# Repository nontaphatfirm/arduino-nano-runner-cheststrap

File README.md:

# Arduino Nano Runner Cheststrap

A wearable sensor system for runner form analysis built on the **Arduino Nano 33 BLE Sense Rev1**.  
Mounts on the chest or torso and streams 9-axis IMU data at 20 Hz to a Web Serial dashboard for real-time feedback.

---

## What It Measures

| Signal | Sensor | Insight |
|---|---|---|
| Acceleration (XYZ) | LSM9DS1 accelerometer (built-in) | Impact force, vertical oscillation, lean |
| Rotation rate (XYZ) | LSM9DS1 gyroscope (built-in) | Trunk lean, roll, yaw drift |
| Magnetic heading | LSM9DS1 magnetometer (built-in) | Absolute orientation reference |
| Ambient sound | OJFF14 analog sound sensor | Sound level / step rhythm |
| Visual capture | OV7675 camera | Keyframe image on demand |

---

## Hardware

### Main Board
**Arduino Nano 33 BLE Sense Rev1** (ABX00031) — Nordic nRF52480, ARM Cortex-M4F @ 64 MHz, 1 MB Flash / 256 KB RAM

Built-in sensors used:

| Chip | Function | I²C Address |
|---|---|---|
| LSM9DS1 | 9-axis IMU (accel + gyro + mag) | — (via library) |
| MP34DT05 | MEMS microphone | — (PDM) |
| APDS-9960 | Gesture / ambient light | 0x39 |
| ATECC608A | Crypto co-processor | — |

### External Sensors

| Component | Connection | Notes |
|---|---|---|
| OJFF14 Sound Sensor | S → A7, + → 3V3, − → GND | 3.3V supply; Nano analog pins are NOT 5V tolerant |
| OV7675 Camera | Arduino Tiny Machine Learning Shield | 8-bit DVP, SCCB config |

### Available Modulino Modules (Arduino Plug and Make Kit)
Connects to **Arduino UNO Q** via Qwiic chain (`Wire1`). Use Modulino library address in code — not the hardware scan address.

| Module | Chip | I²C Address | Specs |
|---|---|---|---|
| DISTANCE | VL53L4CDV0DH/1 (ToF laser) | 0x29 | 0–1200 mm, ±7 mm accuracy |
| THERMO | HS3003 | 0x44 | −40–125°C ±0.25°C / 0–100% RH ±2.8% |
| MOVEMENT | LSM6DSOXTR (6-axis IMU) | 0x6A | ±2–16 g / ±125–2000 dps |
| PIXELS | 8× LC8822-2020 RGB LEDs | 0x6C | 8-bit per channel, individually addressable |
| BUZZER | PKLCS1212E4001 passive buzzer | 0x3C | 31 Hz – 4186 Hz |
| KNOB | Quadrature rotary encoder | 0x76 | Rotary + press |
| BUTTONS | 3× SPST + LEDs | 0x7C | Tactile navigation |

---

## sensors-test — Main Sketch

> **This is the primary code for the project.**

```
sensors-test/
├── sensors_test/
│   └── sensors_test.ino   ← Arduino sketch (IMU + sound, 20 Hz JSON over Serial)
└── dashboard.html          ← Web Serial dashboard (Chrome / Edge)
```

### Serial Output

Streams newline-delimited JSON at 115200 baud, 20 Hz:

```json
{"type":"data","t":12345,"ax":0.12,"ay":0.03,"az":9.81,"gx":0.01,"gy":0.02,"gz":0.00,"mx":12.0,"my":4.0,"mz":39.0,"magReady":true,"soundRaw":2048,"soundPeak":120,"soundVolts":1.65,"soundLevel":0.13}
```

| Field | Unit | Description |
|---|---|---|
| ax, ay, az | m/s² | Acceleration |
| gx, gy, gz | rad/s | Angular velocity |
| mx, my, mz | µT | Magnetic field |
| soundRaw | 12-bit ADC avg | Mean ADC reading across 32 samples |
| soundPeak | 12-bit ADC pp | Peak-to-peak amplitude |
| soundVolts | V | Average voltage at A7 |
| soundLevel | 0–1 | Normalized sound activity |

### Dashboard Features
- Live XYZ acceleration charts
- Orientation: lean, roll, yaw
- Dead-reckoned 3D position estimate (integrate accel → velocity → displacement)
- Step cadence estimate from acceleration magnitude peaks
- Sound level visualization with sensitivity slider

### Required Libraries

Install via Arduino Library Manager:

| Board | Library |
|---|---|
| Nano 33 BLE Sense **Rev1** (default) | `Arduino_LSM9DS1` |
| Rev2 | `Arduino_BMI270_BMM150` — set `SENSOR_BOARD_REV 2` in sketch |

### Quick Start

1. Install `Arduino_LSM9DS1` from Arduino Library Manager.
2. Open `sensors-test/sensors_test/sensors_test.ino`.
3. Select board: **Arduino Nano 33 BLE**.
4. Upload.
5. Open `sensors-test/dashboard.html` in **Chrome** or **Edge**.
6. Click **Connect Serial** → select the Arduino port.
7. Hold the board still → click **Reset Tracking**.
8. Move like a runner torso: lean, bounce, side sway.

### OJFF14 Wiring

| OJFF14 pin | Nano 33 BLE Sense |
|---|---|
| S | A7 |
| + | 3V3 |
| − | GND |

> If powering OJFF14 from 5V, use a voltage divider or level shifter on the signal line — Nano 33 BLE analog inputs are not 5V tolerant.

---

## Repository Layout

| Path | Description |
|---|---|
| `sensors-test/` | **Main sketch + Web Serial dashboard** |
| `hardware/` | Datasheets (UNO Q, Modulino kit, Nano 33 BLE, OV7675, OJFF14) |
| `HARDWARE.md` | Full sensor specs, wiring, I²C addresses |
| `hardware-specs.md` | Concise hardware specification tables |
| `hardware-guide.md` | Beginner-friendly hardware walkthrough |
| `CLAUDE.md` | Project context |

---

## Board Identification

This project targets **Rev1** specifically (original Nano 33 BLE Sense).

USB descriptor confirms Rev1:
```
idVendor  : 0x2341  (Arduino)
idProduct : 0x805A
bcdDevice : 0x0101  (v1.01)
```

Rev2 uses different IMU chips (BMI270 + BMM150) — set `SENSOR_BOARD_REV 2` in the sketch if using Rev2.

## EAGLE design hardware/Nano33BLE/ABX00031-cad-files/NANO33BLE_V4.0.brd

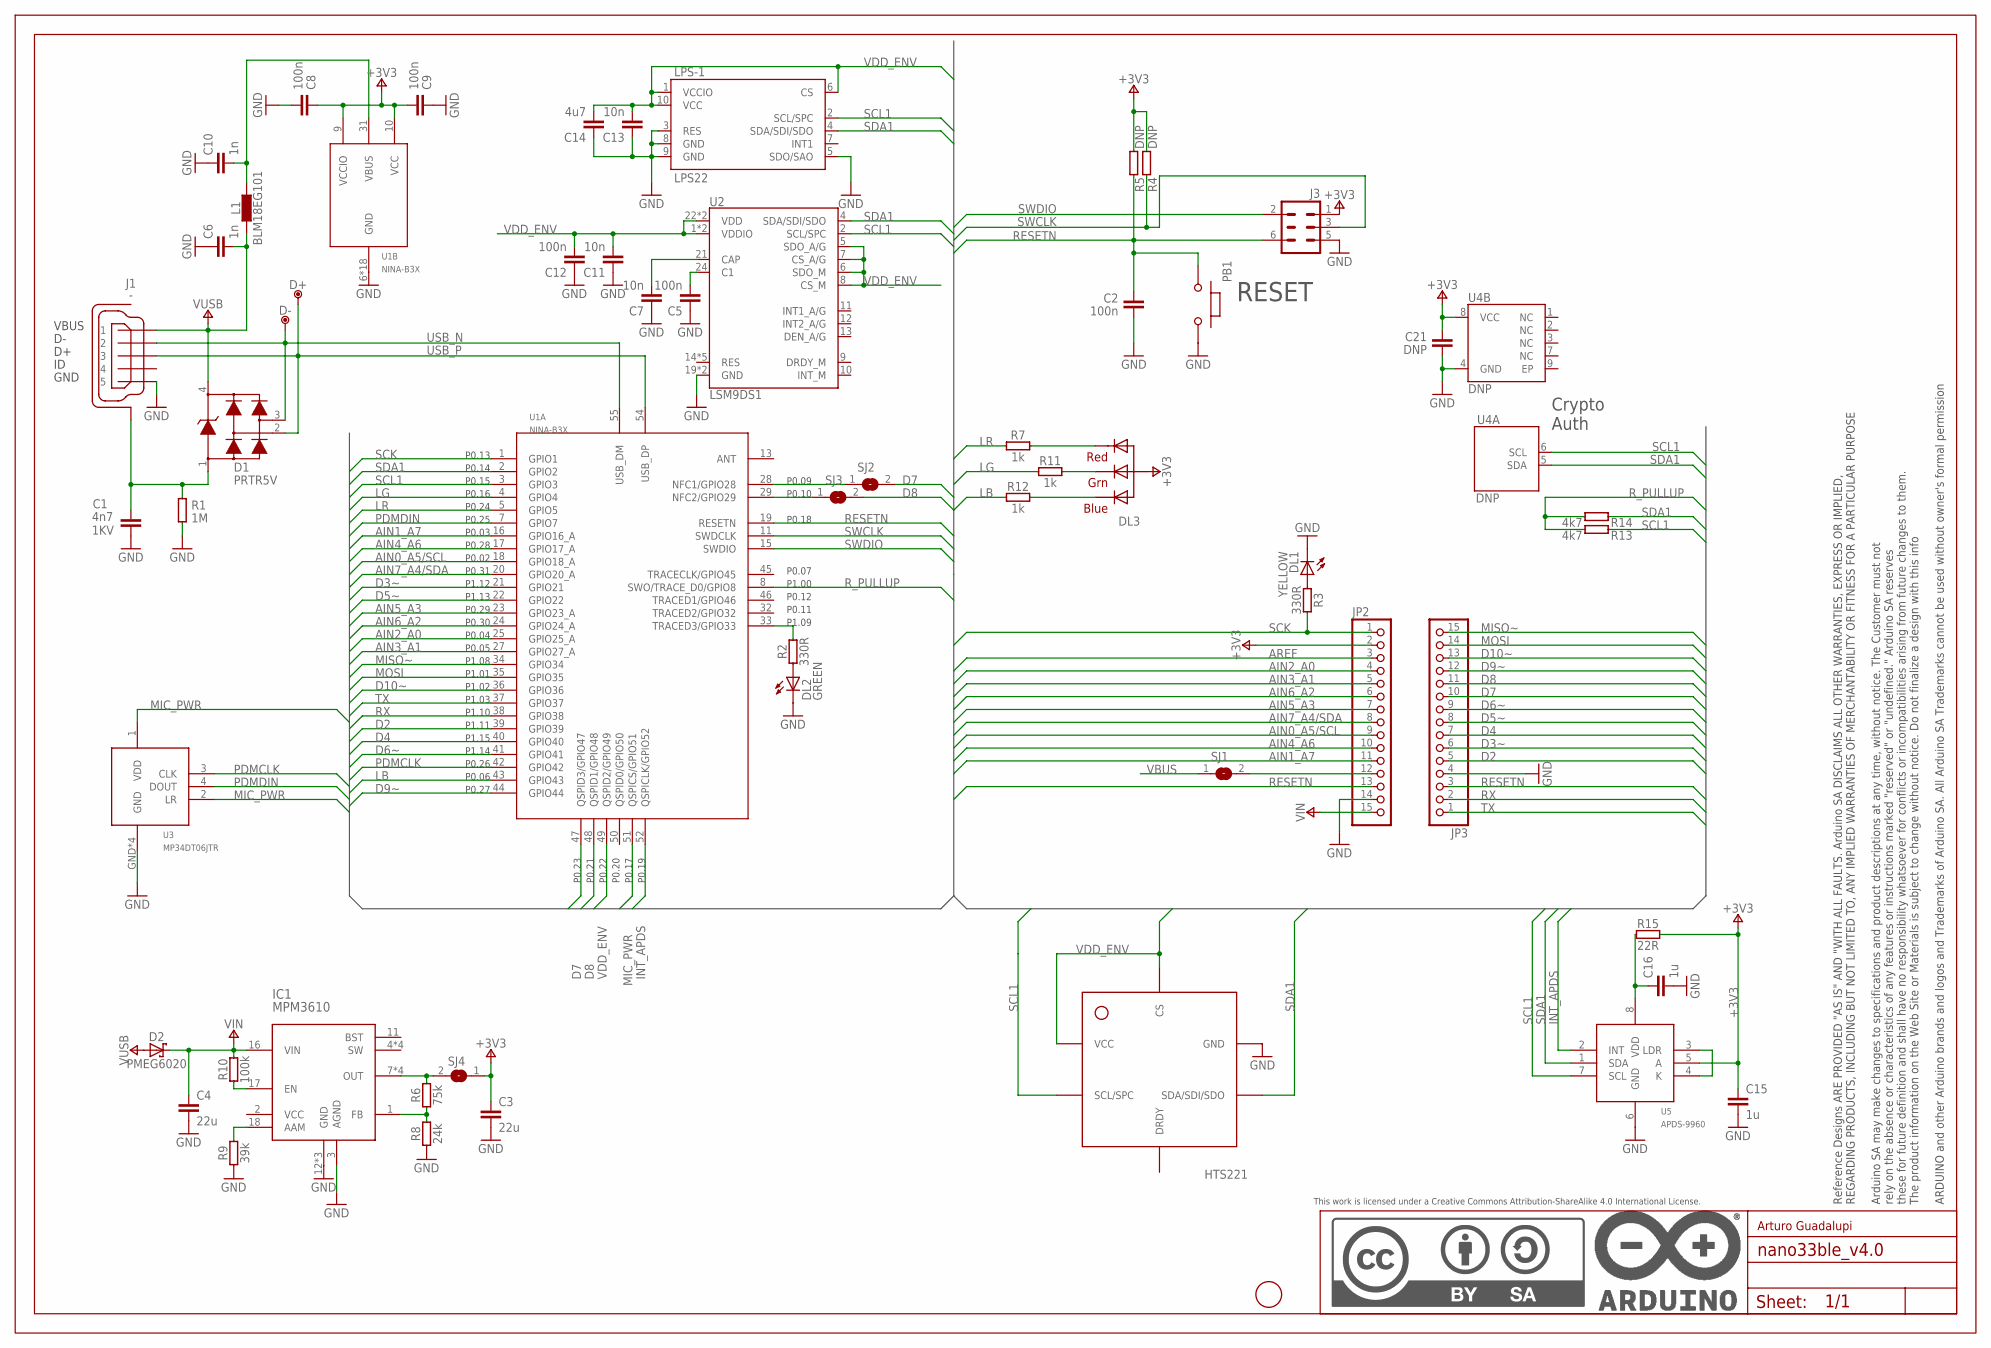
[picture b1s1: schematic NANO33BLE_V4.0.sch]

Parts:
C1: 4n7; 0805-R2013X50N; VOLTAGE 1KV
C2, C5, C8, C9, C12: 100n; 0402-1005X55N
C3, C4: 22u; 0805-R2013X50N
C6, C10: 1n; 0402-1005X55N
C7, C11, C13: 10n; 0402-1005X55N
C14: 4u7; 0402-1005X55N
C15, C16: 1u; 0402-1005X55N
C21: DNP; 0402-1005X55N
D1: PRTR5V; SOT190P230X110-4N
D2: PMEG6020; SODFL3517X110N
D+: DNP; TP-1.00MM
D-: DNP; TP-1.00MM
DL1: YELLOW; LEDC1608X80N-AK
DL2: GREEN; LEDC1608X80N-AK
DL3: -; SMLP34RGB2W
FD1: DNP; FD-1-1.5
FRAME1: DNP; FRAME
HS-1: HTS221
IC1: MPM3610
J1: -; ZX62-AB-5PA
J3: DNP; 2X03-TP1
JP2, JP3: PINHD-1X15-CASTELLATED; 1X15-CASTELL
L1: BLM18EG101; 0603-1608X90N
LPS-1: LPS22; LPS22H
PB1: TACTILE3NO_SH; C&K_PTS820_NO_SH
R1: 1M; 0402-1005X55N
R2, R3: 330R; 0402-1005X55N
R4, R5: DNP; 0402-1005X55N
R6: 75k; 0402-1005X55N
R7, R11, R12: 1k; 0402-1005X55N
R8: 24k; 0402-1005X55N
R9: 39k; 0402-1005X55N
R10: 100k; 0402-1005X55N
R13, R14: 4k7; 0402-1005X55N
R15: 22R; 0402-1005X55N
SJ1, SJ2, SJ3, SJ4: DNP; SJ
U1: NINA-B3X
U2: LSM9DS1; LSM9DS1_TEMP_LGA24-8X4
U3: MP34DT06JTR; HCLGA
U4: DNP; SON50P300X200X60-9N-EP160X140
U5: APDS-9960; APDS9960

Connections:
+3V3: C3.1, C8.1, C9.2, C15.1, C21.1, DL3.1 (A), J3.1, JP2.2, R4.2, R5.2, R15.2, SJ4.1, U1.9 (VCCIO), U1.10 (VCC), U4.8 (VCC), U5.5 (A)
AIN0_A5/SCL: JP2.9, U1.18 (GPIO18_A)
AIN1_A7: JP2.11, U1.16 (GPIO16_A)
AIN2_A0: JP2.4, U1.25 (GPIO25_A)
AIN3_A1: JP2.5, U1.27 (GPIO27_A)
AIN4_A6: JP2.10, U1.17 (GPIO17_A)
AIN5_A3: JP2.7, U1.23 (GPIO23_A)
AIN6_A2: JP2.6, U1.24 (GPIO24_A)
AIN7_A4/SDA: JP2.8, U1.20 (GPIO20_A)
AREF: JP2.3
D2: JP3.5, U1.39 (GPIO39)
D3~: JP3.6, U1.21 (GPIO21)
D4: JP3.7, U1.40 (GPIO40)
D5~: JP3.8, U1.22 (GPIO22)
D6~: JP3.9, U1.41 (GPIO41)
D7: JP3.10, SJ2.2, U1.47 (QSPID3/GPIO47)
D8: JP3.11, SJ3.2, U1.48 (QSPID1/GPIO48)
D9~: JP3.12, U1.44 (GPIO44)
D10~: JP3.13, U1.36 (GPIO36)
GND: C1.2, C2.2, C3.2, C4.2, C5.1, C6.1, C7.1, C8.2, C9.1, C10.1, C11.1, C12.1, C13.1, C14.1, C15.2, C16.2, C21.2, DL1.C, DL2.C, HS-1.P$5.GND (GND), IC1.3 (AGND), IC1.12 (GND), IC1.13 (GND), IC1.14 (GND), J1.5, J3.5, JP2.14, JP3.4, LPS-1.3 (RES), LPS-1.5 (SDO/SAO), LPS-1.8 (GND), LPS-1.9 (GND), PB1.6 (2), R1.1, R8.1, R9.1, U1.6 (GND), U1.12 (GND), U1.14 (GND), U1.26 (GND), U1.30 (GND), U1.53 (GND), U1.GND@1 (GND), U1.GND@2 (GND), U1.GND@3 (GND), U1.GND@4 (GND), U1.GND@5 (GND), U1.GND@6 (GND), U1.GND@7 (GND), U1.GND@8 (GND), U1.GND@9 (GND), U1.GND@10 (GND), U1.GND@11 (GND), U1.GND@12 (GND), U2.19 (GND), U2.20 (GND), U3.GND, U3.GND@2 (GND), U3.GND@3 (GND), U3.GND@4 (GND), U4.4 (GND), U5.6 (GND)
INT_APDS: U1.52 (QSPICLK/GPIO52), U5.2 (INT)
LB: R12.1, U1.43 (GPIO43)
LG: R11.1, U1.4 (GPIO4)
LR: R7.1, U1.5 (GPIO5)
MIC_PWR: U1.51 (QSPICS/GPIO51), U3.1 (VDD), U3.2 (LR)
MISO~: JP3.15, U1.34 (GPIO34)
MOSI: JP3.14, U1.35 (GPIO35)
unnamed: C1.1, D1.1, J1.6 (SH), J1.7 (SH), J1.8 (SH), J1.9 (SH), J1.10 (SH), J1.11 (SH), R1.2
unnamed: DL2.A, R2.1
unnamed: DL1.A, R3.1
unnamed: C5.2, U2.24 (C1)
unnamed: IC1.1 (FB), R6.1, R8.2
unnamed: IC1.18 (AAM), R9.2
unnamed: IC1.17 (EN), R10.1
unnamed: C7.2, U2.21 (CAP)
unnamed: U5.3 (LDR), U5.4 (K)
unnamed: R2.2, U1.33 (TRACED3/GPIO33)
unnamed: DL3.3 (BLUE_C), R12.2
unnamed: DL3.2 (RED_C), R7.2
unnamed: DL3.4 (GREEN_C), R11.2
unnamed: JP2.12, SJ1.2
unnamed: C16.1, R15.1, U5.8 (VDD)
unnamed: IC1.7 (OUT), IC1.8 (OUT), IC1.9 (OUT), IC1.20 (OUT), R6.2, SJ4.2
NFC1: SJ2.1, U1.28 (NFC1/GPIO28)
NFC2: SJ3.1, U1.29 (NFC2/GPIO29)
PDMCLK: U1.42 (GPIO42), U3.3 (CLK)
PDMDIN: U1.7 (GPIO7), U3.4 (DOUT)
RESETN: C2.1, J3.6, JP2.13, JP3.3, PB1.5 (1), R5.1, U1.19 (RESETN)
RX: JP3.2, U1.38 (GPIO38)
R_PULLUP: R13.2, R14.2, U1.8 (SWO/TRACE_D0/GPIO8)
SCK: JP2.1, R3.2, U1.1 (GPIO1)
SCL1: HS-1.P$2.SCL/SPC (SCL/SPC), LPS-1.2 (SCL/SPC), R13.1, U1.3 (GPIO3), U2.2 (SCL/SPC), U4.6 (SCL), U5.7 (SCL)
SDA1: HS-1.P$4.SDA/SDI/SDO (SDA/SDI/SDO), LPS-1.4 (SDA/SDI/SDO), R14.1, U1.2 (GPIO2), U2.4 (SDA/SDI/SDO), U4.5 (SDA), U5.1 (SDA)
SWCLK: J3.3, R4.1, U1.11 (SWDCLK)
SWDIO: J3.2, U1.15 (SWDIO)
TX: JP3.1, U1.37 (GPIO37)
USB_N: D1.3, D-.X, J1.2, U1.55 (USB_DM)
USB_P: D1.2, D+.X, J1.3, U1.54 (USB_DP)
VBUS: C10.2, L1.2, SJ1.1, U1.31 (VBUS)
VDD_ENV: C11.2, C12.2, C13.2, C14.2, HS-1.P$1.VDD (VCC), HS-1.P$6.CS (CS), LPS-1.1 (VCCIO), LPS-1.6 (CS), LPS-1.10 (VCC), U1.49 (QSPID2/GPIO49), U2.1 (VDDIO), U2.3 (VDDIO), U2.5 (SDO_A/G), U2.6 (SDO_M), U2.7 (CS_A/G), U2.8 (CS_M), U2.22 (VDD), U2.23 (VDD)
VIN: C4.1, D2.C, IC1.16 (VIN), JP2.15, R10.2
VUSB: C6.2, D1.4, D2.A, J1.1, L1.1

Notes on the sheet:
RESET
Crypto Auth
Arturo Guadalupi
HTS221

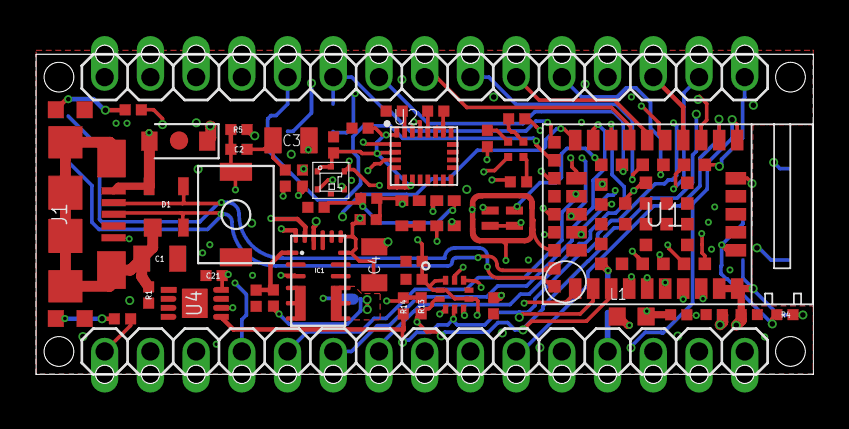
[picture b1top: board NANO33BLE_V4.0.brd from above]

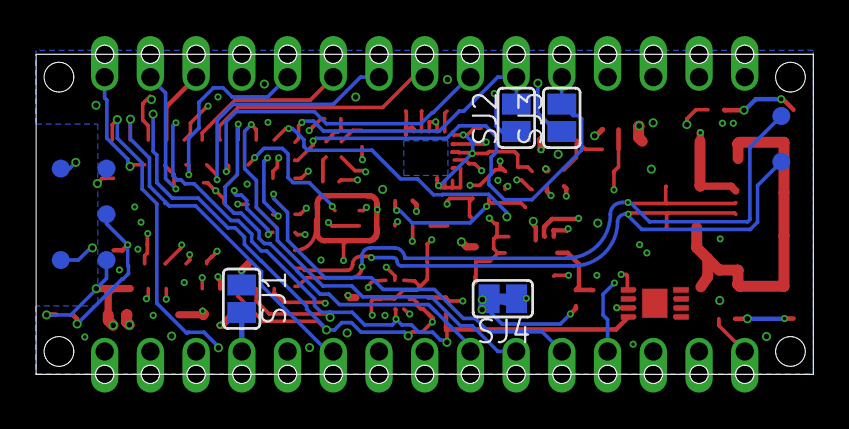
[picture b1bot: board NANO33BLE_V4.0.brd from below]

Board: 4 copper layers, 43.2 x 17.8 mm, 59 parts (4 on the bottom side), 61 nets.

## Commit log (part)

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2026-05-28 Fix FormWings BLE livestream parsing
2026-05-28 Reduce BLE livestream lag

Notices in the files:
hardware/Nano33BLE/ABX00031-cad-files/NANO33BLE_V4.0.brd:
Copyright (c) 2016-2017 Arduino LLC.  All right reserved. EAGLE Design Rules
parts and their libraries:
Arduino-utility: This work is licensed under a Creative Commons Attribution-ShareAlike 4.0 International License.
Arduino-ucs: Copyright (c) 2016-2017 Arduino LLC.  All right reserved.
